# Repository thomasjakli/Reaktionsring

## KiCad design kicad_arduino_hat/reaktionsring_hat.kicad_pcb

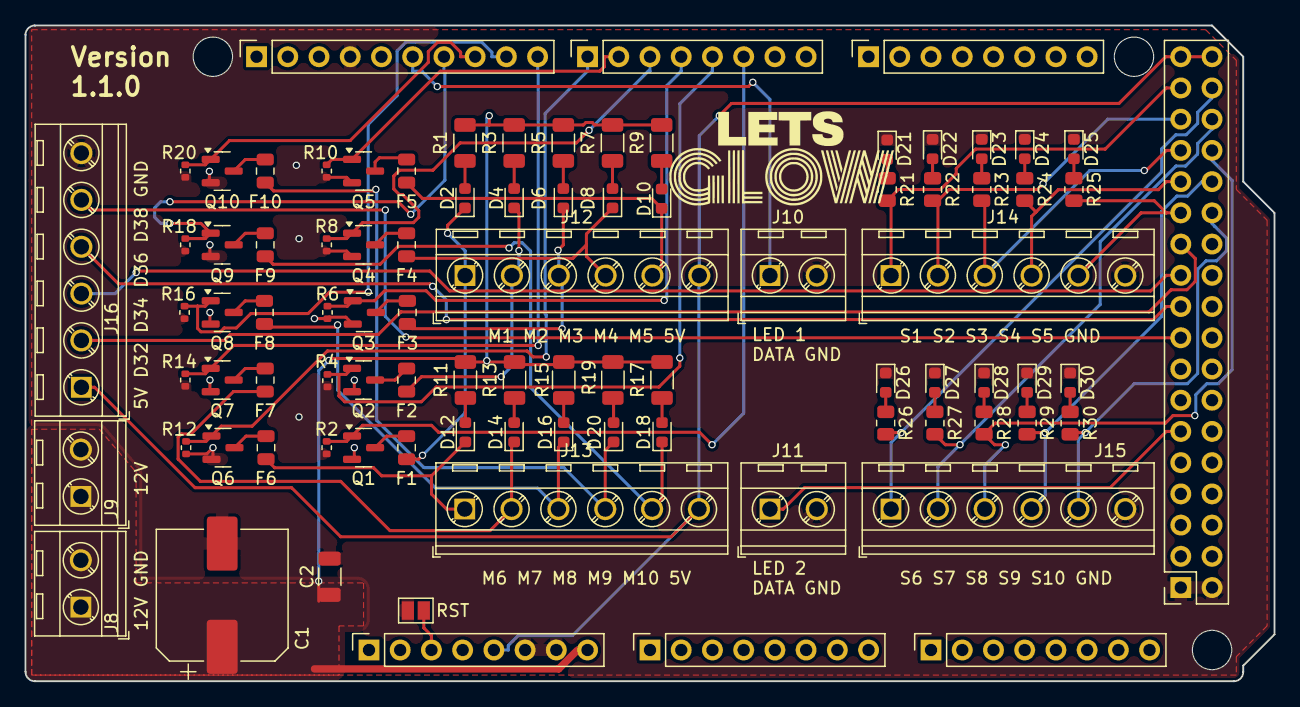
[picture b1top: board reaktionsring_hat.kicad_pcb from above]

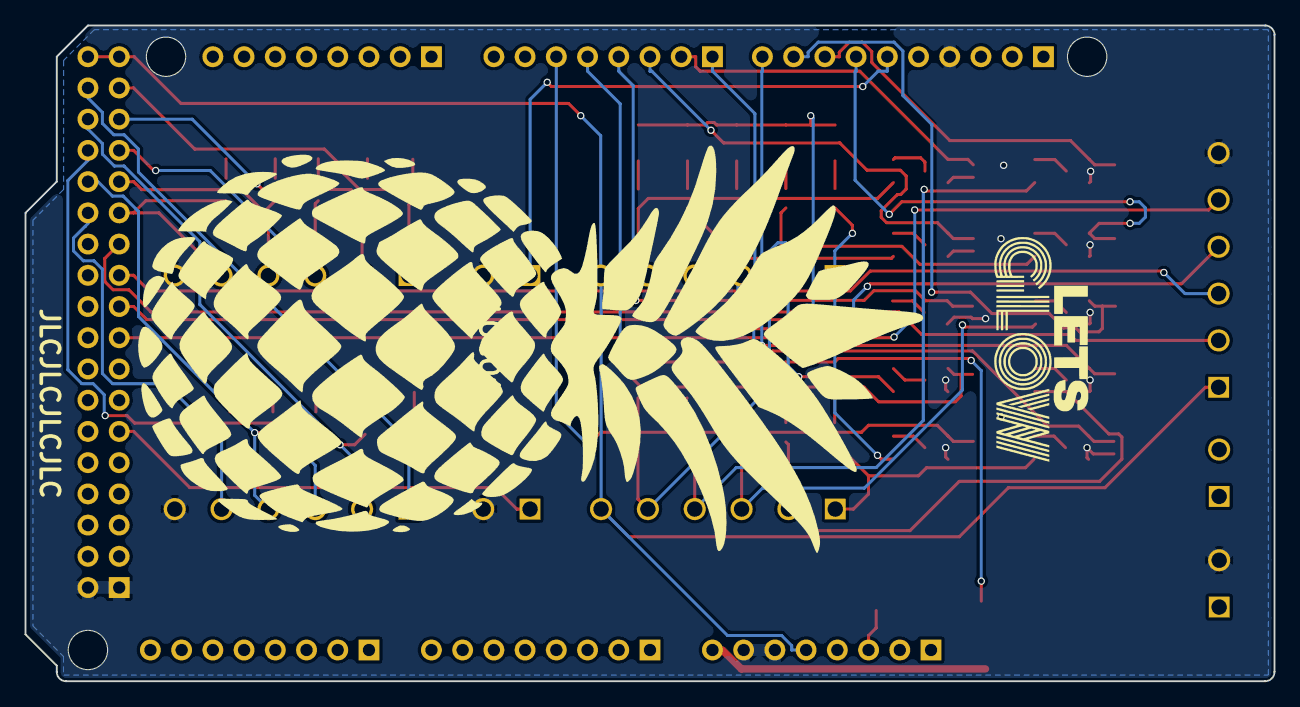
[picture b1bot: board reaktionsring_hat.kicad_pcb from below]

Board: 2 copper layers, 101.6 x 53.3 mm, 95 parts (2 on the bottom side), 70 nets.

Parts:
C1: 1000u; CP_Elec_10x10.5
C2: 10u; C_1206_3216Metric
D2, D4, D6, D8, D10, D12, D14, D16, D18, D20, D21, D22, D23, D24, D25, D26, D27, D28, D29, D30: LED; LED_0603_1608Metric
F1, F2, F3, F4, F5, F6, F7, F8, F9, F10: 300m; Fuse_0805_2012Metric
J1: Power; PinSocket_1x08_P2.54mm_Vertical
J2: PWM; PinSocket_1x10_P2.54mm_Vertical
J3, J5: Analog; PinSocket_1x08_P2.54mm_Vertical
J4: PWM; PinSocket_1x08_P2.54mm_Vertical
J6: Communication; PinSocket_1x08_P2.54mm_Vertical
J7: Digital; PinSocket_2x18_P2.54mm_Vertical
J8, J9, J10, J11: Terminal_1x2; WJ15EDGVC-3.81-2P
J12, J13, J14, J15, J16: Terminal_1x6; WJ15EDGVC-3.81-6P
LOGO1: LOGO; pineapple_outline
LOGO2, LOGO3: LOGO; letsglow_logo
MH1, MH5, MH6: MountingHole_3.2mm
Q1, Q2, Q3, Q4, Q5, Q6, Q7, Q8, Q9, Q10: 2N7002K; SOT-23
R1, R3, R5, R7, R9, R11, R13, R15, R17, R19: 470R; R_1206_3216Metric
R2, R4, R6, R8, R10, R12, R14, R16, R18, R20: 10k; R_0402_1005Metric
R21, R22, R23, R24, R25, R26, R27, R28, R29, R30: 150R; R_0805_2012Metric
RST: SolderJumper-2_P1.3mm_Open_Pad1.0x1.5mm

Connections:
+5V: J1.5, J7.35, J7.36, J12.6, J13.6, J16.1
/22: J7.33, J14.1, R21.2
/23: J7.34, J15.1, R26.2
/24: J7.31, J14.2, R22.2
/25: J7.32, J15.2, R27.2
/26: J7.29, J14.3, R23.2
/27: J7.30, J15.3, R28.2
/28: J7.27, J14.4, R24.2
/29: J7.28, J15.4, R29.2
/30: J7.25, J14.5, R25.2
/31: J7.26, J15.5, R30.2
/32: J7.23, J16.2
/34: J7.21, J16.3
/36: J7.19, J16.4
/38: J7.17, J16.5
/*2: J4.6, Q1.1 (G), R2.1
/*3: J4.5, Q2.1 (G), R4.1
/*4: J4.4, Q3.1 (G), R6.1
/*5: J4.3, Q4.1 (G), R8.1
/*6: J4.2, Q5.1 (G), R10.1
/*7: J4.1, Q6.1 (G), R12.1
/*8: J2.10, Q7.1 (G), R14.1
/*9: J2.9, Q8.1 (G), R16.1
/*10: J2.8, Q10.1 (G), R20.1
/*11: J2.7, Q9.1 (G), R18.1
/*12: J2.6, J10.1
/*44: J7.11, J11.1
/M1: D2.1 (K), F1.1, J12.1
/M2: D4.1 (K), F2.1, J12.2
/M3: D6.1 (K), F3.1, J12.3
/M4: D8.1 (K), F4.1, J12.4
/M5: D10.1 (K), F5.1, J12.5
/M6: D12.1 (K), F6.1, J13.1
/M7: D14.1 (K), F7.1, J13.2
/M8: D16.1 (K), F8.1, J13.3
/M9: D20.1 (K), F10.1, J13.4
/M10: D18.1 (K), F9.1, J13.5
/~RESET: J1.3, RST.2
GND: C1.2, C2.2, D21.1 (K), D22.1 (K), D23.1 (K), D24.1 (K), D25.1 (K), D26.1 (K), D27.1 (K), D28.1 (K), D29.1 (K), D30.1 (K), J1.6, J1.7, J2.4, J7.1, J7.2, J8.2, J10.2, J11.2, J14.6, J15.6, J16.6, Q1.2 (S), Q2.2 (S), Q3.2 (S), Q4.2 (S), Q5.2 (S), Q6.2 (S), Q7.2 (S), Q8.2 (S), Q9.2 (S), Q10.2 (S), R2.2, R4.2, R6.2, R8.2, R10.2, R12.2, R14.2, R16.2, R18.2, R20.2, RST.1
unnamed: D2.2 (A), R1.2
unnamed: D4.2 (A), R3.2
unnamed: D6.2 (A), R5.2
unnamed: D8.2 (A), R7.2
unnamed: D10.2 (A), R9.2
unnamed: D12.2 (A), R11.2
unnamed: D14.2 (A), R13.2
unnamed: D16.2 (A), R15.2
unnamed: D18.2 (A), R17.2
unnamed: D20.2 (A), R19.2
unnamed: D21.2 (A), R21.1
unnamed: D22.2 (A), R22.1
unnamed: D23.2 (A), R23.1
unnamed: D24.2 (A), R24.1
unnamed: D25.2 (A), R25.1
unnamed: D26.2 (A), R26.1
unnamed: D27.2 (A), R27.1
unnamed: D28.2 (A), R28.1
unnamed: D29.2 (A), R29.1
unnamed: D30.2 (A), R30.1
unnamed: F1.2, Q1.3 (D)
unnamed: F2.2, Q2.3 (D)
unnamed: F3.2, Q3.3 (D)
unnamed: F4.2, Q4.3 (D)
unnamed: F5.2, Q5.3 (D)
unnamed: F6.2, Q6.3 (D)
unnamed: F7.2, Q7.3 (D)
unnamed: F8.2, Q8.3 (D)
unnamed: F9.2, Q9.3 (D)
unnamed: F10.2, Q10.3 (D)
VCC: C1.1, C2.1, J1.8, J8.1, J9.1, J9.2, R1.1, R3.1, R5.1, R7.1, R9.1, R11.1, R13.1, R15.1, R17.1, R19.1

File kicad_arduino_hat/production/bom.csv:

Designator,Footprint,Quantity,Value,LCSC Part #
C1,CP_Elec_10x10.5,1,1000u,C3359
C2,1206,1,10u,C9807
"D10, D12, D14, D16, D18, D2, D20, D21, D22, D23, D24, D25, D26, D27, D28, D29, D30, D4, D6, D8",0603,20,LED,C22371299
"F1, F10, F2, F3, F4, F5, F6, F7, F8, F9",0805,10,300m,C22378356
"J10, J11, J8, J9",WJ15EDGVC-3.81-2P,4,Terminal_1x2,C8396
"J12, J13, J14, J15, J16",WJ15EDGVC-3.81-6P,5,Terminal_1x6,C8415
"Q1, Q10, Q2, Q3, Q4, Q5, Q6, Q7, Q8, Q9",SOT-23,10,2N7002K,C414015
"R1, R11, R13, R15, R17, R19, R3, R5, R7, R9",1206,10,470R,C118071
"R10, R12, R14, R16, R18, R2, R20, R4, R6, R8",0402,10,10k,C25744
"R21, R22, R23, R24, R25, R26, R27, R28, R29, R30",0805,10,150R,C17471
"J17,J18,J19,J20,J21","Conn_01x06_Pin","","","5","","C7247"
"J22,J23,J24,J25","Conn_01x02_Pin","","","4","","C8466"

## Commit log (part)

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2024-12-17 Init Reaktionsring Project
2024-12-17 Add game logic
2024-12-27 Adjust pin assignments to match custom HAT
